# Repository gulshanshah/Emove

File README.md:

# Emove

Connecto is a DIY smart-home automation system built with ESP32, MQTT, Node.js, and React Native. It enables remote relay control through a mobile app, with real-time communication via Socket.IO, OTA firmware updates, and custom KiCad-designed PCBs.

## Repository layout

| Path | What it is |
| --- | --- |
| `myapp/` | React Native (0.78) app for Android and iOS |
| `server/` | Node.js bridge: MQTT ⇄ Socket.IO (Express + socket.io + mqtt) |
| `pcb/` | KiCad projects: `controller/` (main board) and `try/` (prototype) |

## Getting started

### Server

```bash
cd server
npm install
cp .env.example .env    # then fill in your broker credentials
npm start               # listens on http://localhost:3000
```

Configuration is read from `server/.env` (never committed): `MQTT_URL`, `MQTT_USER`, `MQTT_PASS`, optional `PORT`.

The bridge subscribes to `utsav/<hubId>/state` and publishes commands to `utsav/<hubId>/cmd` (payload format `relay<N>=<0|1>`).

### App

```bash
cd myapp
npm install
bundle install && bundle exec pod install   # iOS only
npx react-native run-android                # or run-ios
```

Point the app at your server by updating the `SERVER_URL` constants in the home screen components. Firmware provisioning connects to the device AP at `http://192.168.4.1`.

### PCB

Open `pcb/controller/controller.kicad_pro` with KiCad 8 or newer.

## Platform notes

- Android release signing currently falls back to the debug keystore; generate your own keystore before shipping.
- `google-services.json` and `debug.keystore` are intentionally not committed; add your own under `myapp/android/app/` before building.

## License

MIT — see [LICENSE](LICENSE).

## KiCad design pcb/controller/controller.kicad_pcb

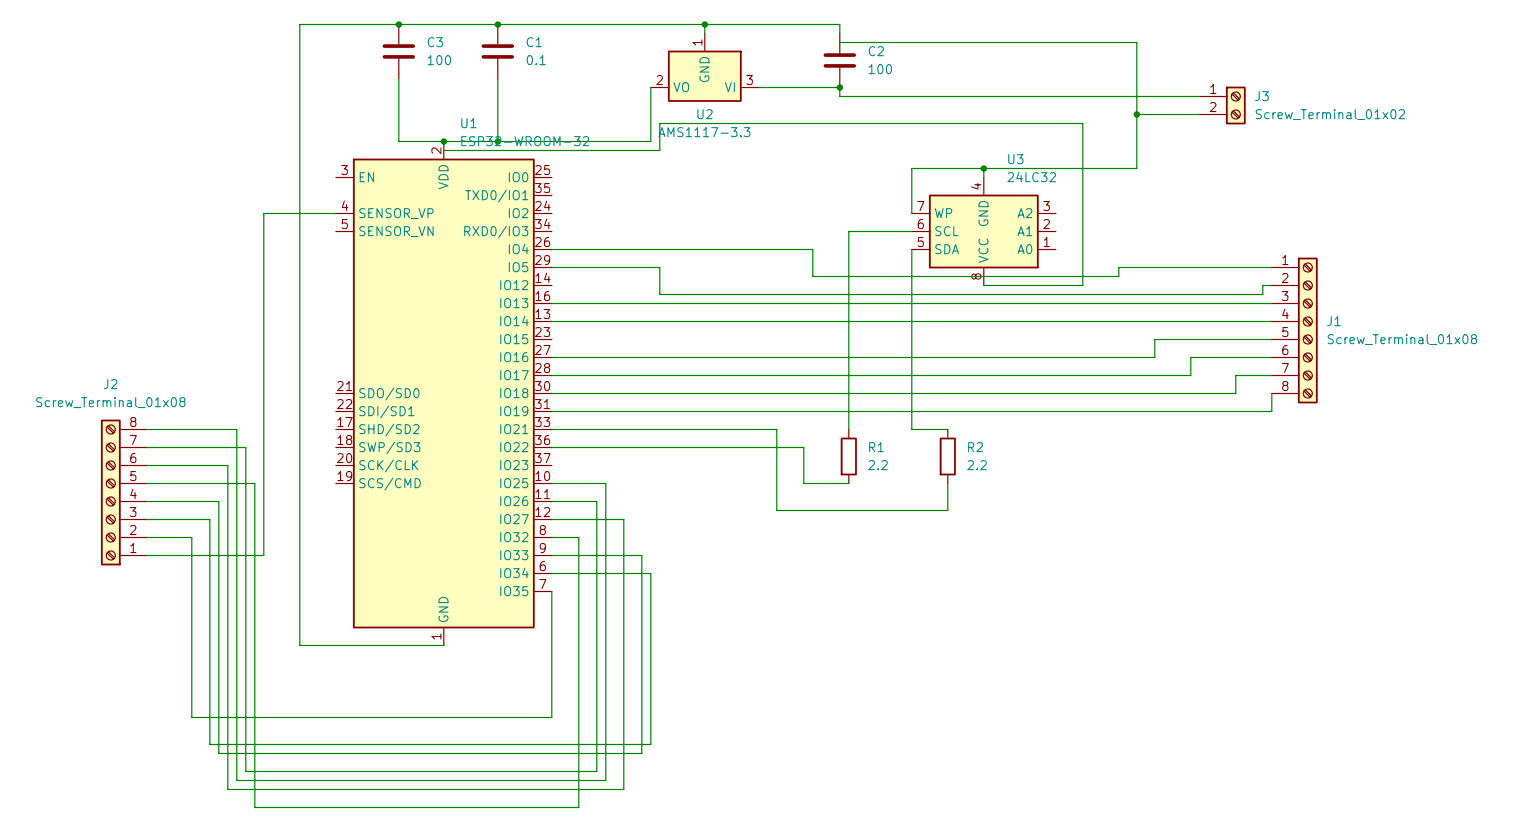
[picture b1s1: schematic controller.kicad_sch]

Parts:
C1: 0.1; C_Disc_D5.0mm_W2.5mm_P2.50mm
C2, C3: 100; C_Radial_D6.3mm_H7.0mm_P2.50mm
J1: Screw_Terminal_01x08; TerminalBlock_Phoenix_MKDS-1,5-8_1x08_P5.00mm_Horizontal
J2: Screw_Terminal_01x08; TerminalBlock_Phoenix_MKDS-1,5-8-5.08_1x08_P5.08mm_Horizont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
J3: Screw_Terminal_01x02; TerminalBlock_MetzConnect_Type011_RT05502HBLC_1x02_P5.00mm_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
R1, R2: 2.2; R_Axial_DIN0207_L6.3mm_D2.5mm_P7.62mm_Horizontal
U1: ESP32-WROOM-32
U2: AMS1117-3.3; SOT-223-3_TabPin2
U3: 24LC32; SOIC-8_3.9x4.9mm_P1.27mm

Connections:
unnamed: J1.1, U1.26 (IO4)
unnamed: J1.2, U1.29 (IO5)
unnamed: J1.3, U1.16 (IO13)
unnamed: J1.4, U1.13 (IO14)
unnamed: J1.5, U1.27 (IO16)
unnamed: J1.6, U1.28 (IO17)
unnamed: J1.7, U1.30 (IO18)
unnamed: J1.8, U1.31 (IO19)
unnamed: J2.1, U1.4 (SENSOR_VP)
unnamed: J2.2, U1.7 (IO35)
unnamed: J2.3, U1.6 (IO34)
unnamed: J2.4, U1.9 (IO33)
unnamed: J2.5, U1.8 (IO32)
unnamed: J2.6, U1.12 (IO27)
unnamed: J2.7, U1.11 (IO26)
unnamed: J2.8, U1.10 (IO25)
unnamed: C2.1, J3.1, U2.3 (VI)
unnamed: J3.2, U3.4 (GND), U3.7 (WP)
unnamed: R2.2, U1.33 (IO21)
unnamed: R1.2, U1.36 (IO22)
unnamed: C1.2, C3.2, U1.2 (VDD), U2.2 (VO)
unnamed: C1.1, C2.2, C3.1, U1.1 (GND), U1.15 (GND), U1.38 (GND), U1.39 (GND), U2.1 (GND)
unnamed: R1.1, U3.6 (SCL)
unnamed: R2.1, U3.5 (SDA)

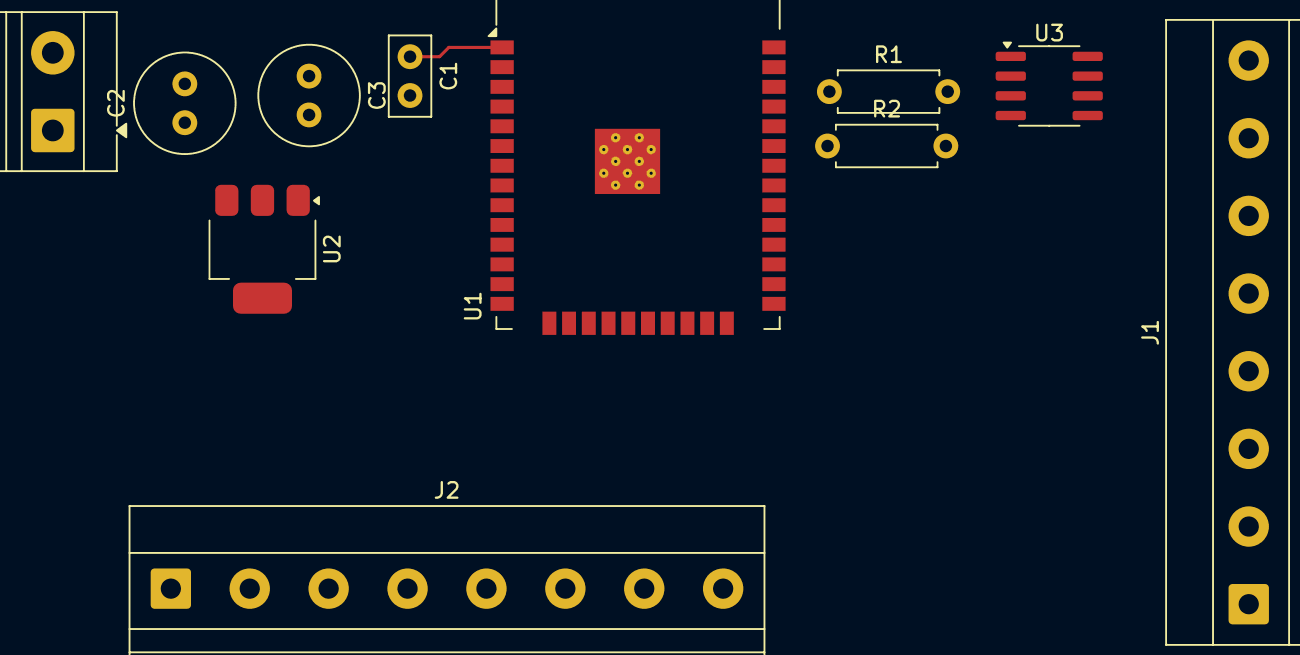
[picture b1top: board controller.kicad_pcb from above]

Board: 2 copper layers, 11 parts (0 on the bottom side), 24 nets.
